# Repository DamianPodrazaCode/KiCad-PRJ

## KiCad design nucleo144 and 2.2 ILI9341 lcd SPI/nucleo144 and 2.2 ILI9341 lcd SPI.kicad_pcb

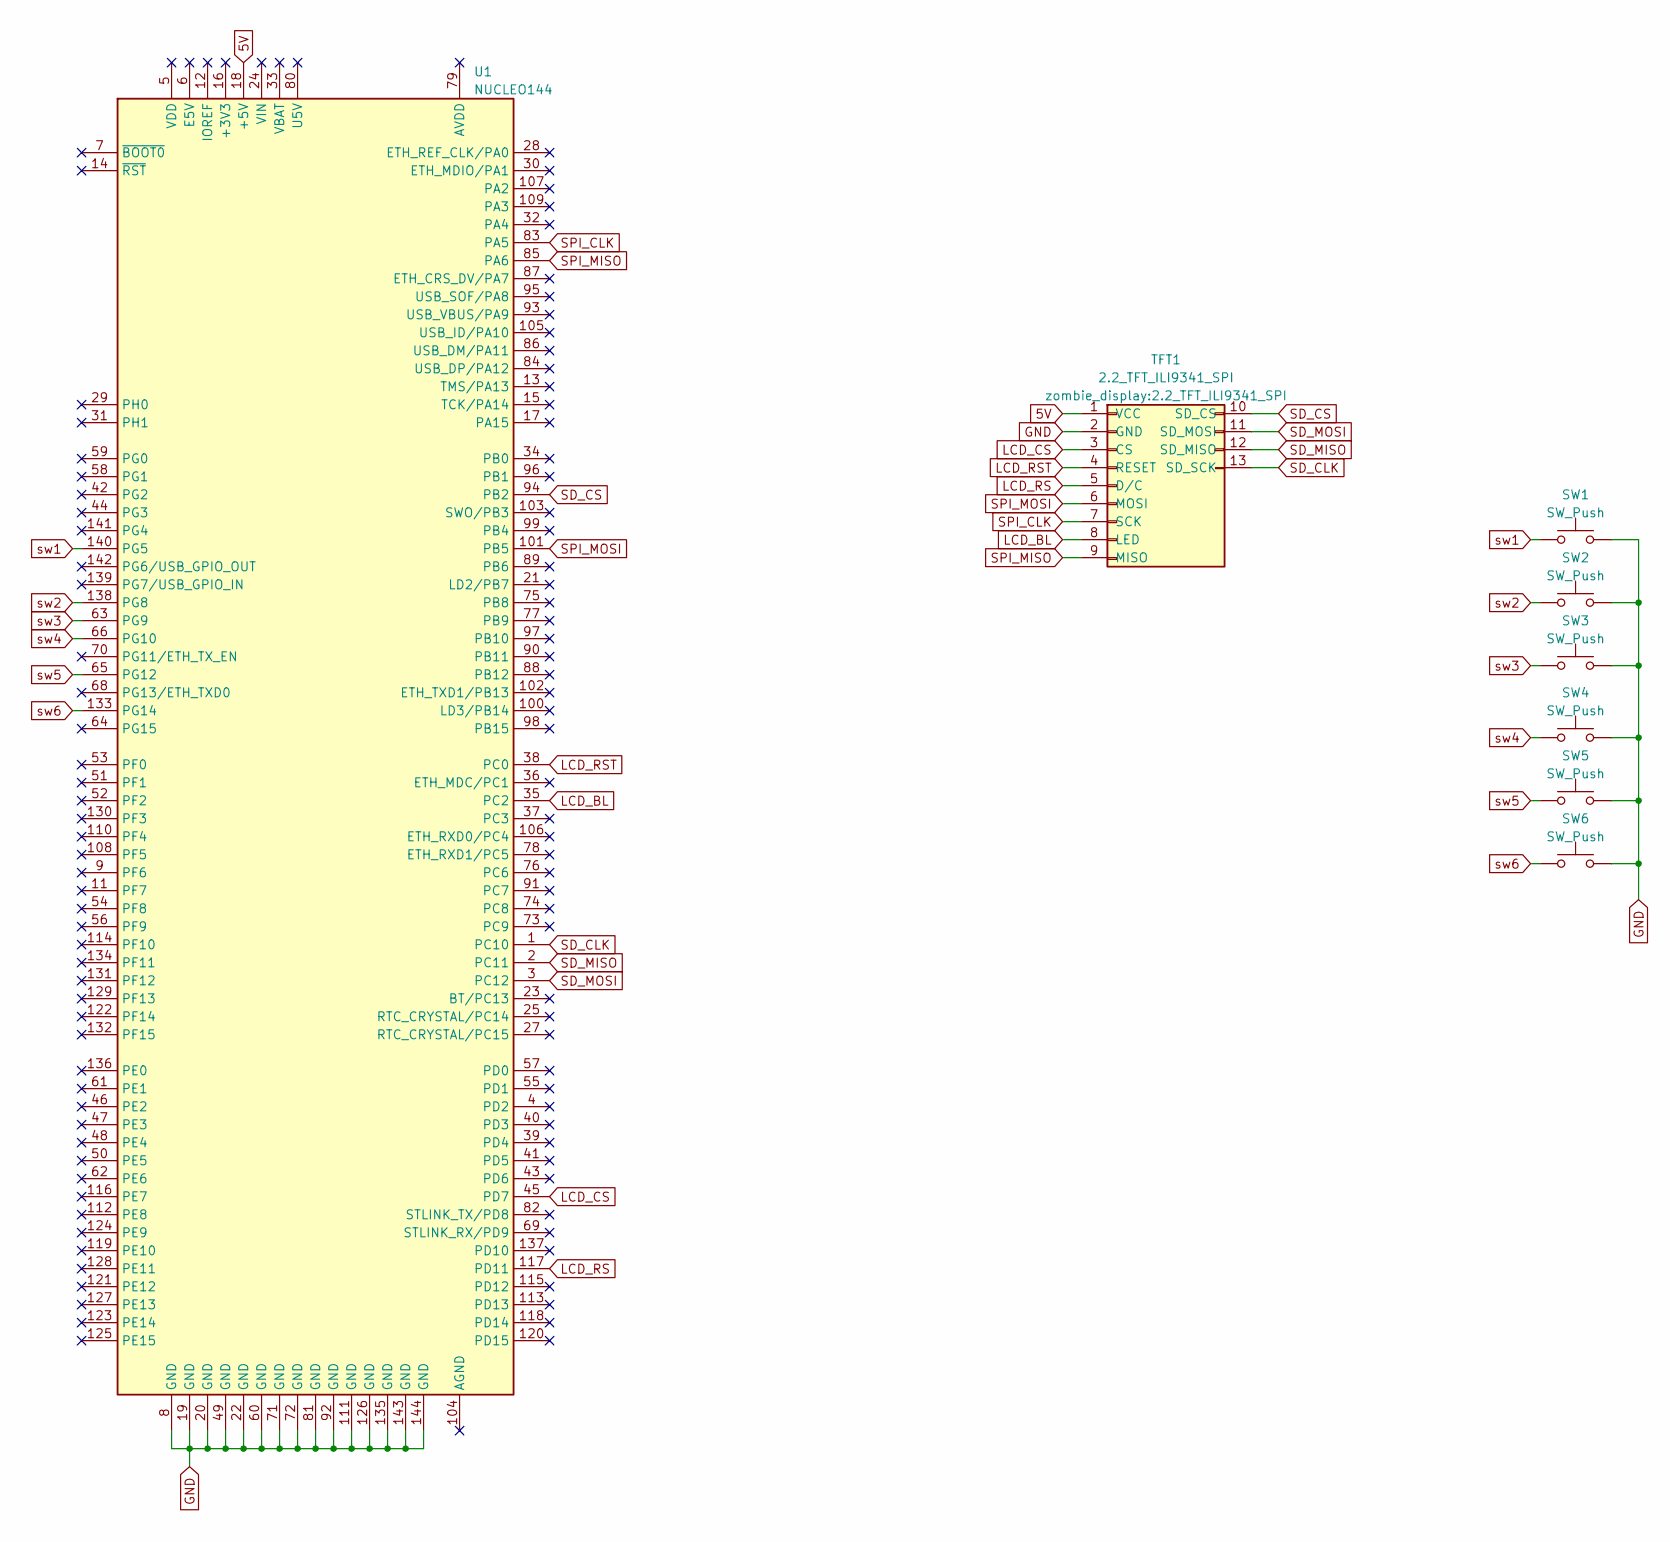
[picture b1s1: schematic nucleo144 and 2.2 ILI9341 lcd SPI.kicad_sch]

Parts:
SW1, SW2, SW3, SW4, SW5, SW6: SW_Push; SW_PUSH_6mm
TFT1: 2.2_TFT_ILI9341_SPI
U1: NUCLEO144; ST_Morpho_Connector_144_Short

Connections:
5V: TFT1.1 (VCC), U1.18 (+5V)
D0: U1.118 (PD14)
D1: U1.120 (PD15)
D2: U1.57 (PD0)
D3: U1.55 (PD1)
D4: U1.116 (PE7)
D5: U1.112 (PE8)
D6: U1.124 (PE9)
D7: U1.119 (PE10)
D8: U1.128 (PE11)
D9: U1.121 (PE12)
D10: U1.127 (PE13)
D11: U1.123 (PE14)
D12: U1.125 (PE15)
D13: U1.82 (STLINK_TX/PD8)
D14: U1.69 (STLINK_RX/PD9)
D15: U1.137 (PD10)
F_CS: U1.96 (PB1)
GND: SW1.2, SW2.2, SW3.2, SW4.2, SW5.2, SW6.2, TFT1.2 (GND), U1.8 (GND), U1.19 (GND), U1.20 (GND), U1.22 (GND), U1.49 (GND), U1.60 (GND), U1.71 (GND), U1.72 (GND), U1.81 (GND), U1.92 (GND), U1.111 (GND), U1.126 (GND), U1.135 (GND), U1.143 (GND), U1.144 (GND)
LCD_BL: TFT1.8 (LED), U1.35 (PC2)
LCD_CS: TFT1.3 (CS), U1.45 (PD7)
LCD_RD: U1.39 (PD4)
LCD_RS: TFT1.5 (D/C), U1.117 (PD11)
LCD_RST: TFT1.4 (RESET), U1.38 (PC0)
LCD_WR: U1.41 (PD5)
PEN: U1.37 (PC3)
SD_CLK: TFT1.13 (SD_SCK), U1.1 (PC10)
SD_CS: TFT1.10 (SD_CS), U1.94 (PB2)
SD_MISO: TFT1.12 (SD_MISO), U1.2 (PC11)
SD_MOSI: TFT1.11 (SD_MOSI), U1.3 (PC12)
SPI_CLK: TFT1.7 (SCK), U1.83 (PA5)
SPI_MISO: TFT1.9 (MISO), U1.85 (PA6)
SPI_MOSI: TFT1.6 (MOSI), U1.101 (PB5)
T_CS: U1.109 (PA3)
sw1: SW1.1, U1.140 (PG5)
sw2: SW2.1, U1.138 (PG8)
sw3: SW3.1, U1.63 (PG9)
sw4: SW4.1, U1.66 (PG10)
sw5: SW5.1, U1.65 (PG12)
sw6: SW6.1, U1.133 (PG14)

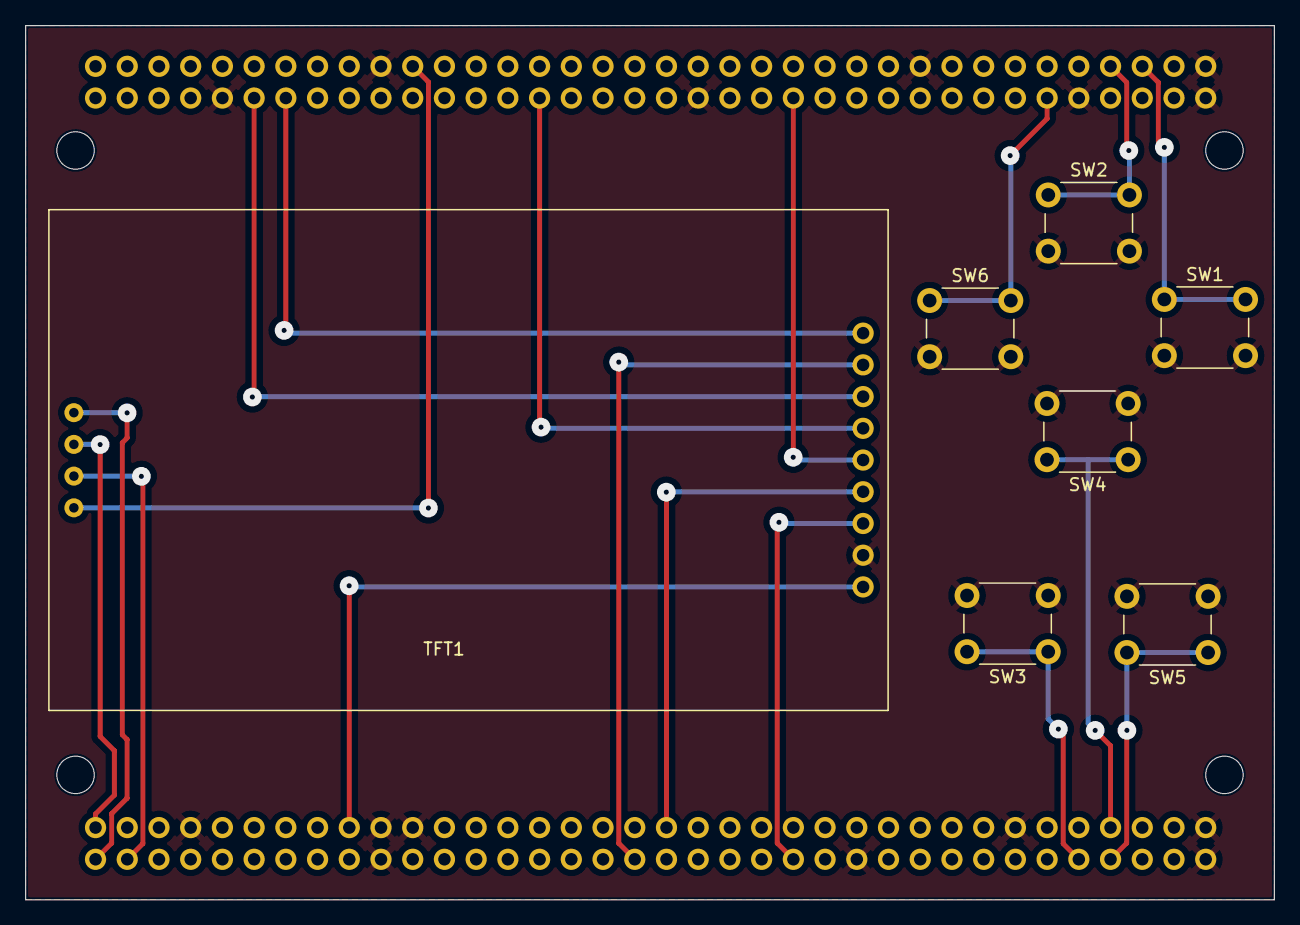
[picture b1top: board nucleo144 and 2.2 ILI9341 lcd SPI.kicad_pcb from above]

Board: 2 copper layers, 100.0 x 70.0 mm, 8 parts (0 on the bottom side), 19 nets.

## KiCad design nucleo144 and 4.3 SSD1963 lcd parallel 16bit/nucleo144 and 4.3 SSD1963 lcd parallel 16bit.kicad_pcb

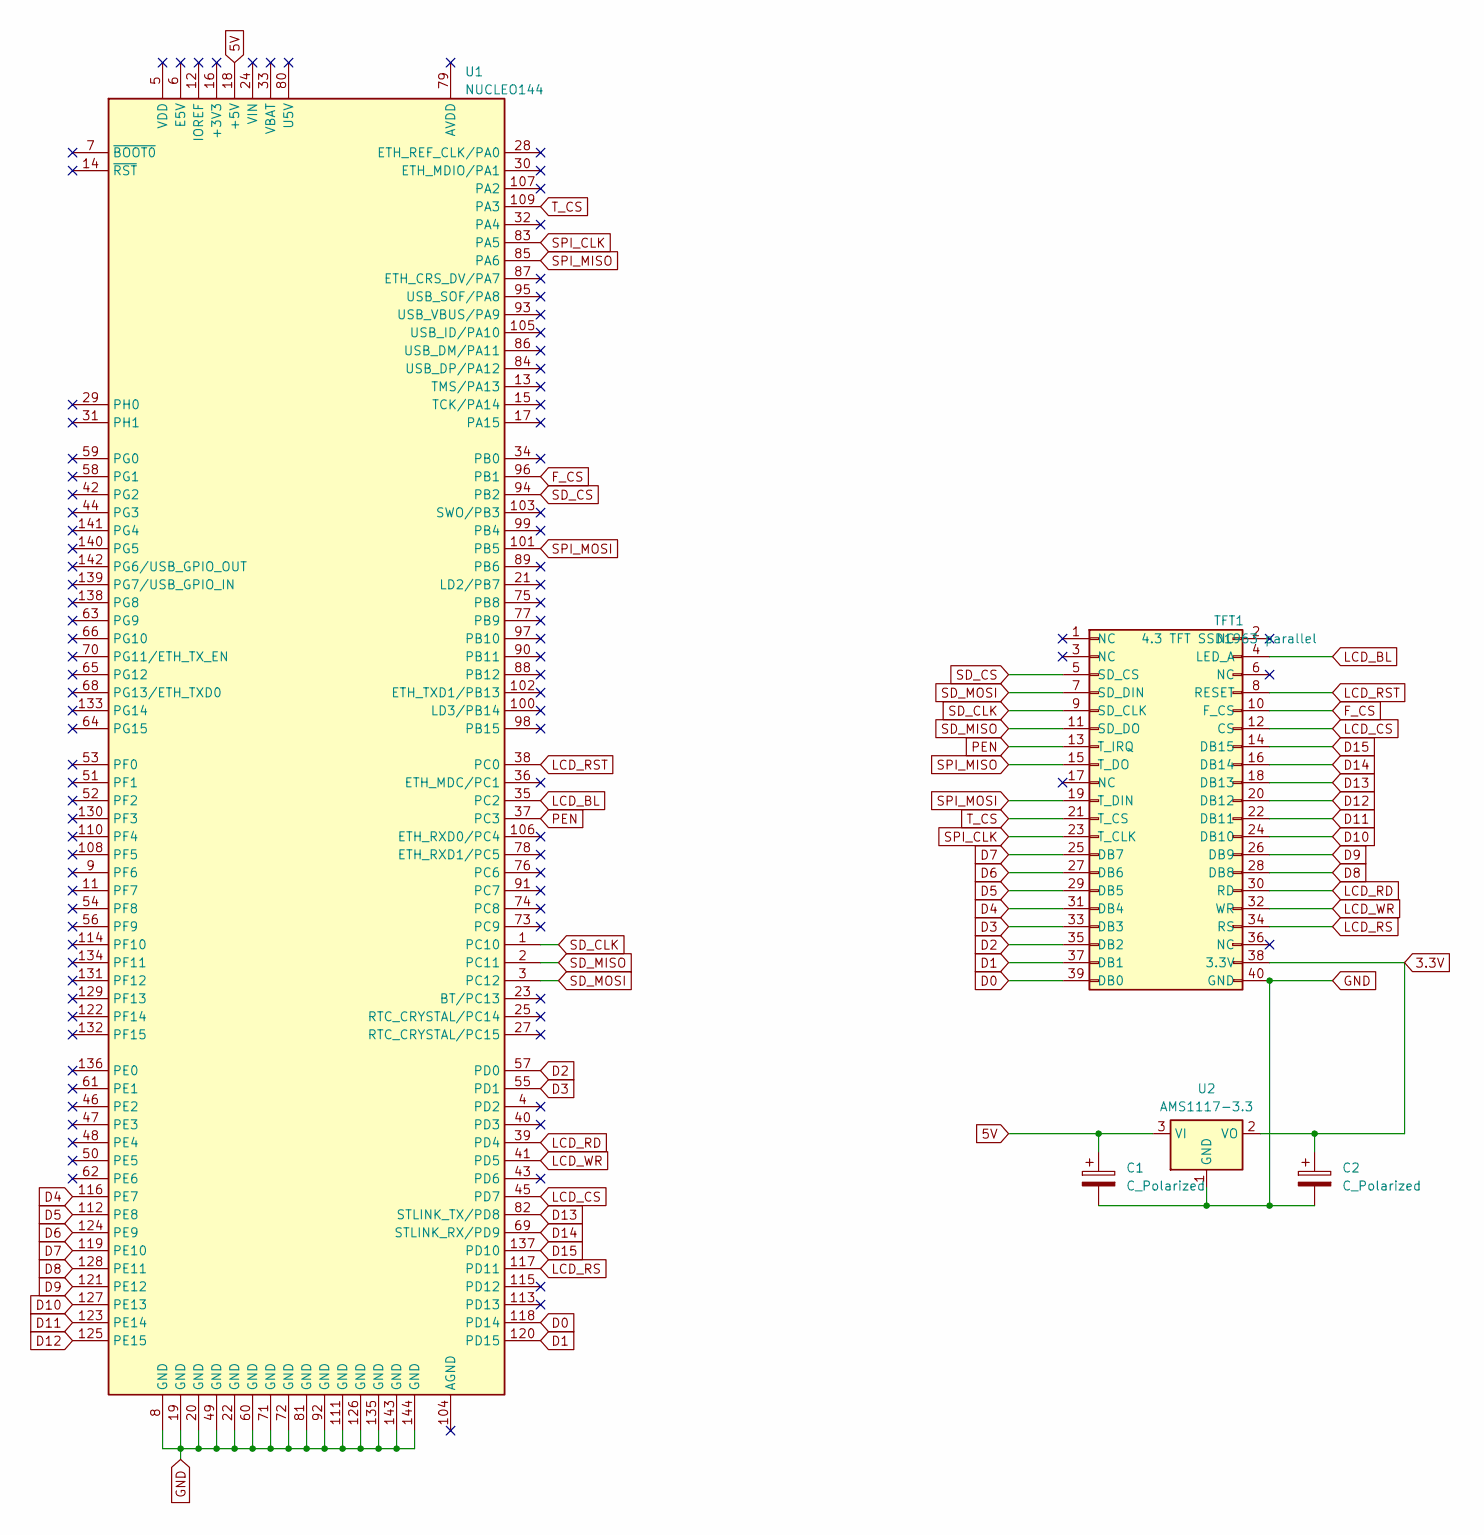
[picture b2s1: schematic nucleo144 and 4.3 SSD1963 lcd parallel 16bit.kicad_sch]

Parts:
C1, C2: C_Polarized; CP_EIA-3528-12_Kemet-T
TFT1: 4.3 TFT SSD1963 parallel; 4.3_TFT_SSD1963
U1: NUCLEO144; ST_Morpho_Connector_144_Short
U2: AMS1117-3.3; SOT-223-3_TabPin2

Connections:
3.3V: C2.1, TFT1.38 (3.3V), U2.2 (VO)
5V: C1.1, U1.18 (+5V), U2.3 (VI)
D0: TFT1.39 (DB0), U1.118 (PD14)
D1: TFT1.37 (DB1), U1.120 (PD15)
D2: TFT1.35 (DB2), U1.57 (PD0)
D3: TFT1.33 (DB3), U1.55 (PD1)
D4: TFT1.31 (DB4), U1.116 (PE7)
D5: TFT1.29 (DB5), U1.112 (PE8)
D6: TFT1.27 (DB6), U1.124 (PE9)
D7: TFT1.25 (DB7), U1.119 (PE10)
D8: TFT1.28 (DB8), U1.128 (PE11)
D9: TFT1.26 (DB9), U1.121 (PE12)
D10: TFT1.24 (DB10), U1.127 (PE13)
D11: TFT1.22 (DB11), U1.123 (PE14)
D12: TFT1.20 (DB12), U1.125 (PE15)
D13: TFT1.18 (DB13), U1.82 (STLINK_TX/PD8)
D14: TFT1.16 (DB14), U1.69 (STLINK_RX/PD9)
D15: TFT1.14 (DB15), U1.137 (PD10)
F_CS: TFT1.10 (F_CS), U1.96 (PB1)
GND: C1.2, C2.2, TFT1.40 (GND), U1.8 (GND), U1.19 (GND), U1.20 (GND), U1.22 (GND), U1.49 (GND), U1.60 (GND), U1.71 (GND), U1.72 (GND), U1.81 (GND), U1.92 (GND), U1.111 (GND), U1.126 (GND), U1.135 (GND), U1.143 (GND), U1.144 (GND), U2.1 (GND)
LCD_BL: TFT1.4 (LED_A), U1.35 (PC2)
LCD_CS: TFT1.12 (CS), U1.45 (PD7)
LCD_RD: TFT1.30 (RD), U1.39 (PD4)
LCD_RS: TFT1.34 (RS), U1.117 (PD11)
LCD_RST: TFT1.8 (RESET), U1.38 (PC0)
LCD_WR: TFT1.32 (WR), U1.41 (PD5)
PEN: TFT1.13 (T_IRQ), U1.37 (PC3)
SD_CLK: TFT1.9 (SD_CLK), U1.1 (PC10)
SD_CS: TFT1.5 (SD_CS), U1.94 (PB2)
SD_MISO: TFT1.11 (SD_DO), U1.2 (PC11)
SD_MOSI: TFT1.7 (SD_DIN), U1.3 (PC12)
SPI_CLK: TFT1.23 (T_CLK), U1.83 (PA5)
SPI_MISO: TFT1.15 (T_DO), U1.85 (PA6)
SPI_MOSI: TFT1.19 (T_DIN), U1.101 (PB5)
T_CS: TFT1.21 (T_CS), U1.109 (PA3)

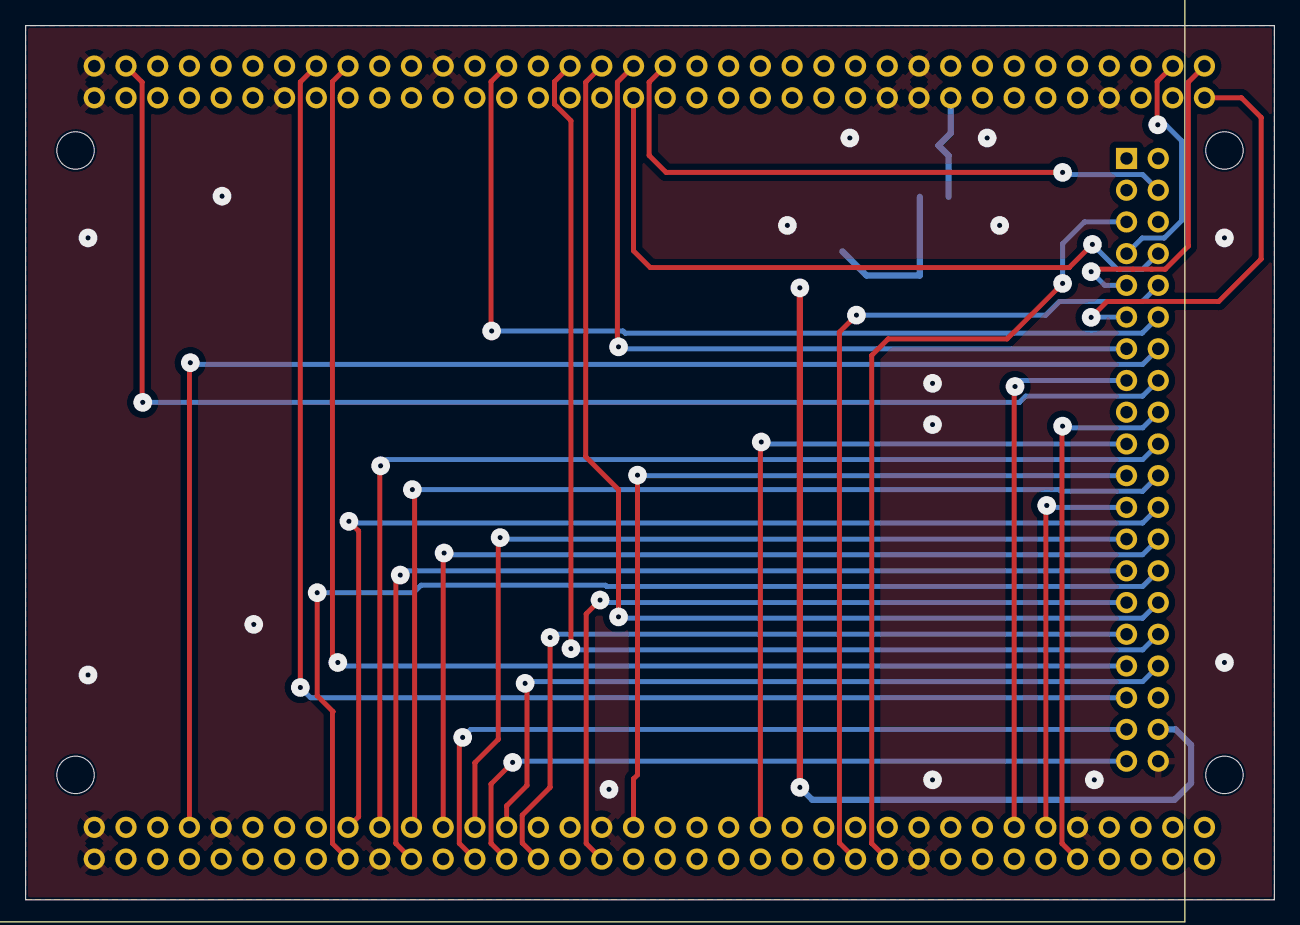
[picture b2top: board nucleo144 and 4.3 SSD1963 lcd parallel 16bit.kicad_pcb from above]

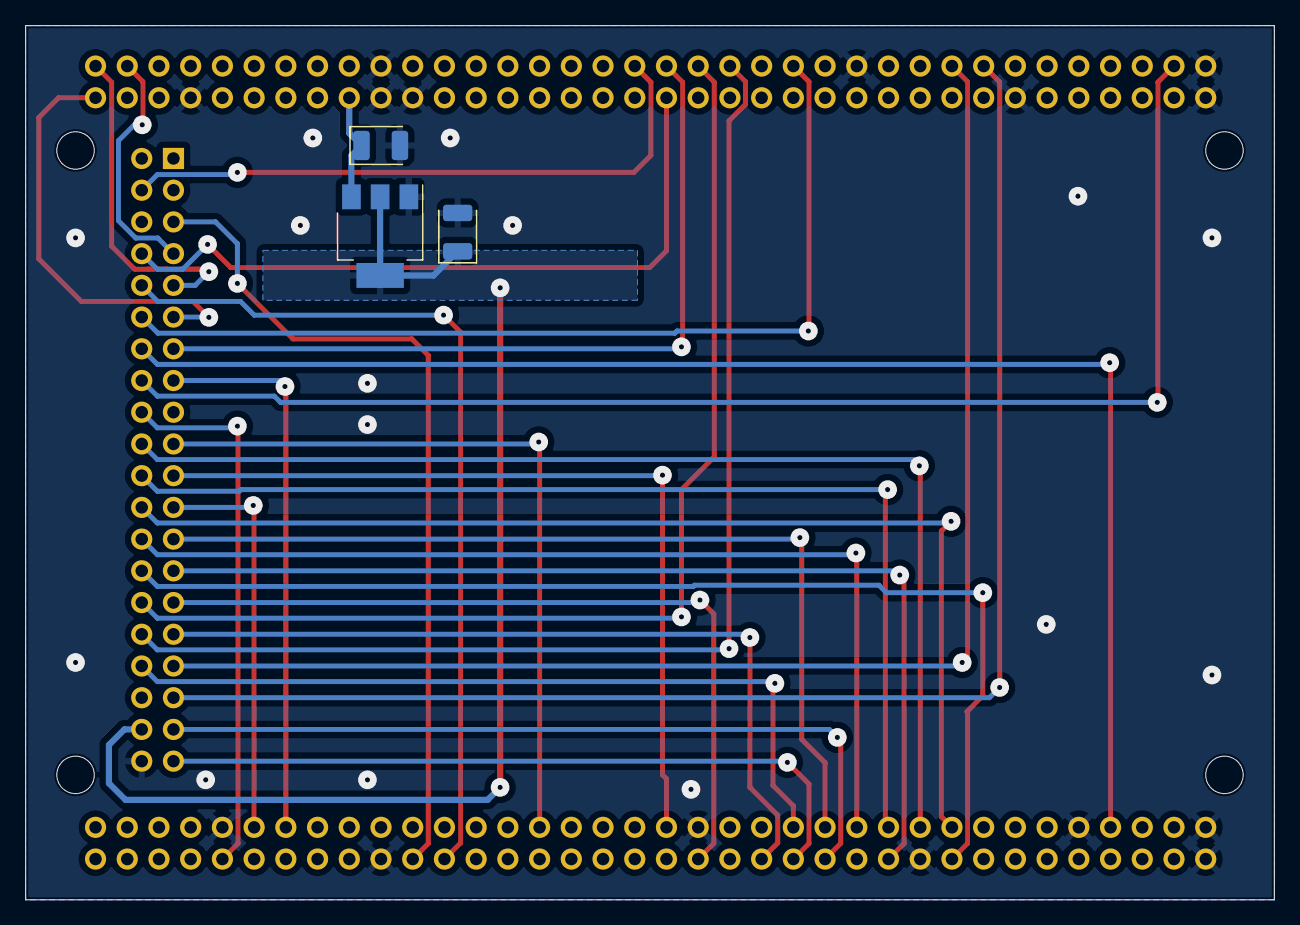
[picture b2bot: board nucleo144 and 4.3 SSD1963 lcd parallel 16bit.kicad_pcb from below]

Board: 2 copper layers, 100.0 x 70.0 mm, 5 parts (3 on the bottom side), 35 nets.

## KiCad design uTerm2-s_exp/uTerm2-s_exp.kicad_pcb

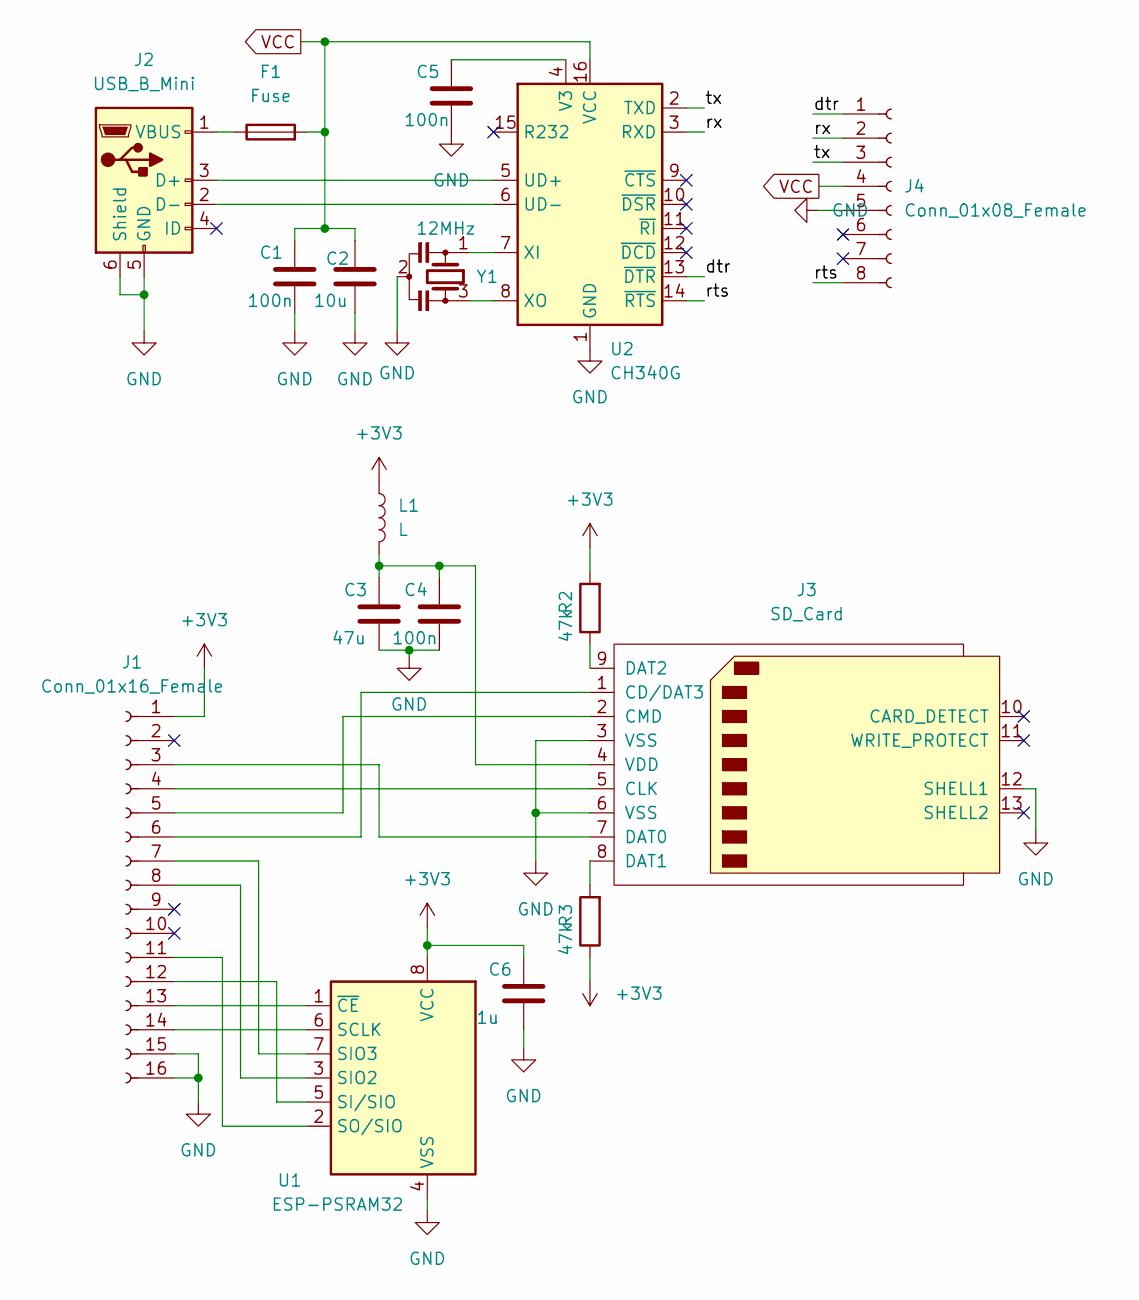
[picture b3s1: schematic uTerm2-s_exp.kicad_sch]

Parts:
C1, C4, C5: 100n; C_1206_3216Metric_Pad1.33x1.80mm_HandSolder
C2: 10u; C_1206_3216Metric_Pad1.33x1.80mm_HandSolder
C3: 47u; CP_EIA-3528-12_Kemet-T_Pad1.50x2.35mm_HandSolder
C6: 1u; C_1206_3216Metric_Pad1.33x1.80mm_HandSolder
F1: Fuse; Fuse_1812_4532Metric_Pad1.30x3.40mm_HandSolder
J1: Conn_01x16_Female; PinSocket_2x08_P2.54mm_Vertical
J2: USB_B_Mini; USB_Mini-B_Lumberg_2486_01_Horizontal
J3: SD_Card; SD_TE_2041021
J4: Conn_01x08_Female; PinSocket_1x08_P2.54mm_Vertical
L1: L; L_1806_4516Metric_Pad1.45x1.90mm_HandSolder
R2, R3: 47k; R_1206_3216Metric_Pad1.30x1.75mm_HandSolder
U1: ESP-PSRAM32; SOIC-8_3.9x4.9mm_P1.27mm
U2: CH340G; SOP-16_3.9x9.9mm_P1.27mm
Y1: 12MHz; Resonator_SMD_Murata_CSTxExxV-3Pin_3.0x1.1mm_HandSoldering

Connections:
+3V3: C6.1, J1.1, L1.1, R2.2, R3.1, U1.8 (VCC)
/dtr: J4.1, U2.13 (~DTR)
/rts: J4.8, U2.14 (~RTS)
/rx: J4.2, U2.3 (RXD)
/tx: J4.3, U2.2 (TXD)
GND: C1.2, C2.2, C3.2, C4.2, C5.2, C6.2, J1.15, J1.16, J2.5 (GND), J2.6 (Shield), J3.3 (VSS), J3.6 (VSS), J3.12 (SHELL1), J4.5, U1.4 (VSS), U2.1 (GND), Y1.2
unnamed: C3.1, C4.1, J3.4 (VDD), L1.2
unnamed: C5.1, U2.4 (V3)
unnamed: F1.1, J2.1 (VBUS)
unnamed: J1.3, J3.7 (DAT0)
unnamed: J1.4, J3.5 (CLK)
unnamed: J1.5, J3.2 (CMD)
unnamed: J1.6, J3.1 (CD/DAT3)
unnamed: J1.7, U1.7 (SIO3)
unnamed: J1.8, U1.3 (SIO2)
unnamed: J1.11, U1.2 (SO/SIO)
unnamed: J1.12, U1.5 (SI/SIO)
unnamed: J1.13, U1.1 (~CE)
unnamed: J1.14, U1.6 (SCLK)
unnamed: J2.2 (D-), U2.6 (UD-)
unnamed: J2.3 (D+), U2.5 (UD+)
unnamed: J3.8 (DAT1), R3.2
unnamed: J3.9 (DAT2), R2.1
unnamed: U2.7 (XI), Y1.1
unnamed: U2.8 (XO), Y1.3
VCC: C1.1, C2.1, F1.2, J4.4, U2.16 (VCC)

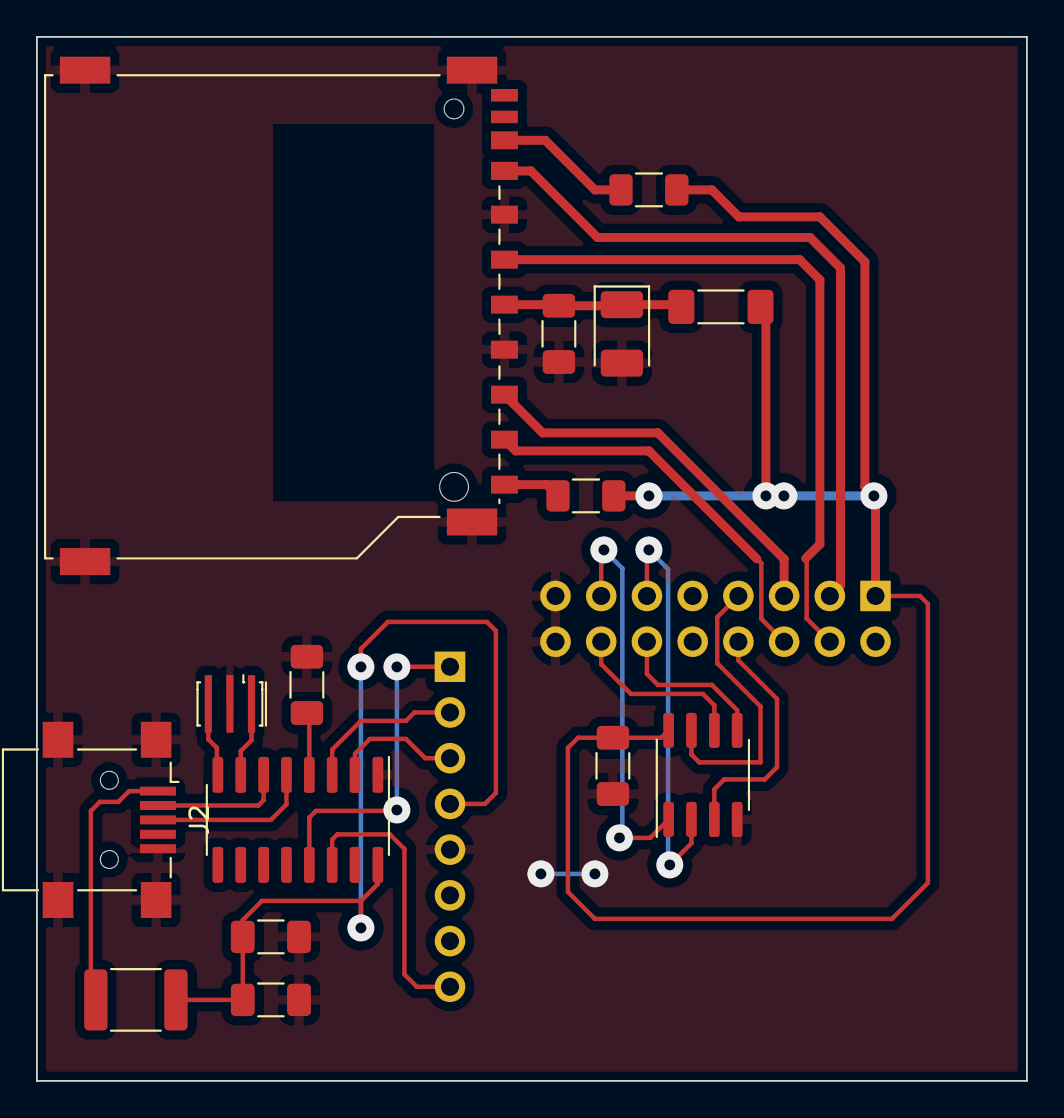
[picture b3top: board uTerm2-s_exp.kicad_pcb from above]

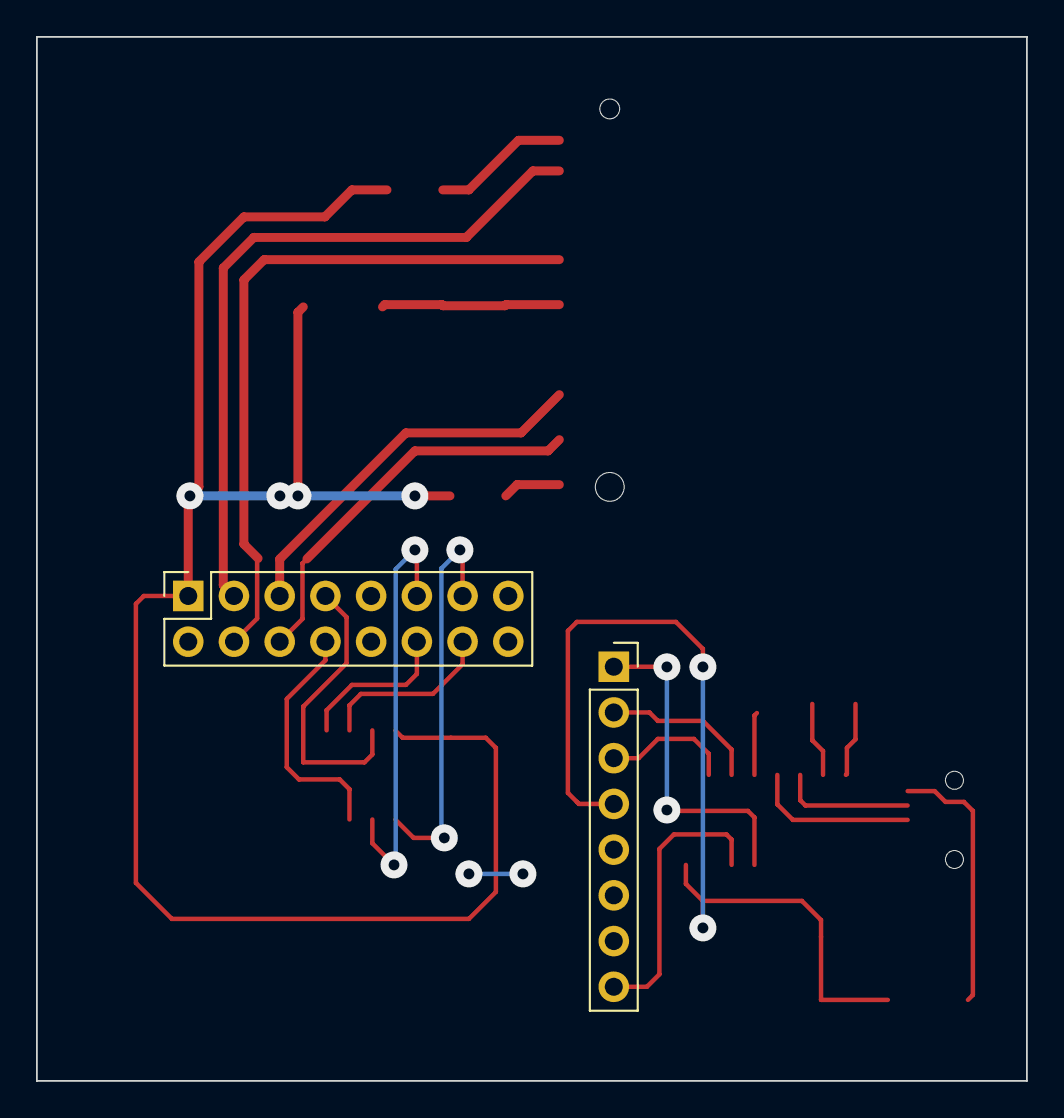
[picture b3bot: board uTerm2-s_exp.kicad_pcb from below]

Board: 2 copper layers, 55.0 x 58.0 mm, 17 parts (2 on the bottom side), 26 nets.

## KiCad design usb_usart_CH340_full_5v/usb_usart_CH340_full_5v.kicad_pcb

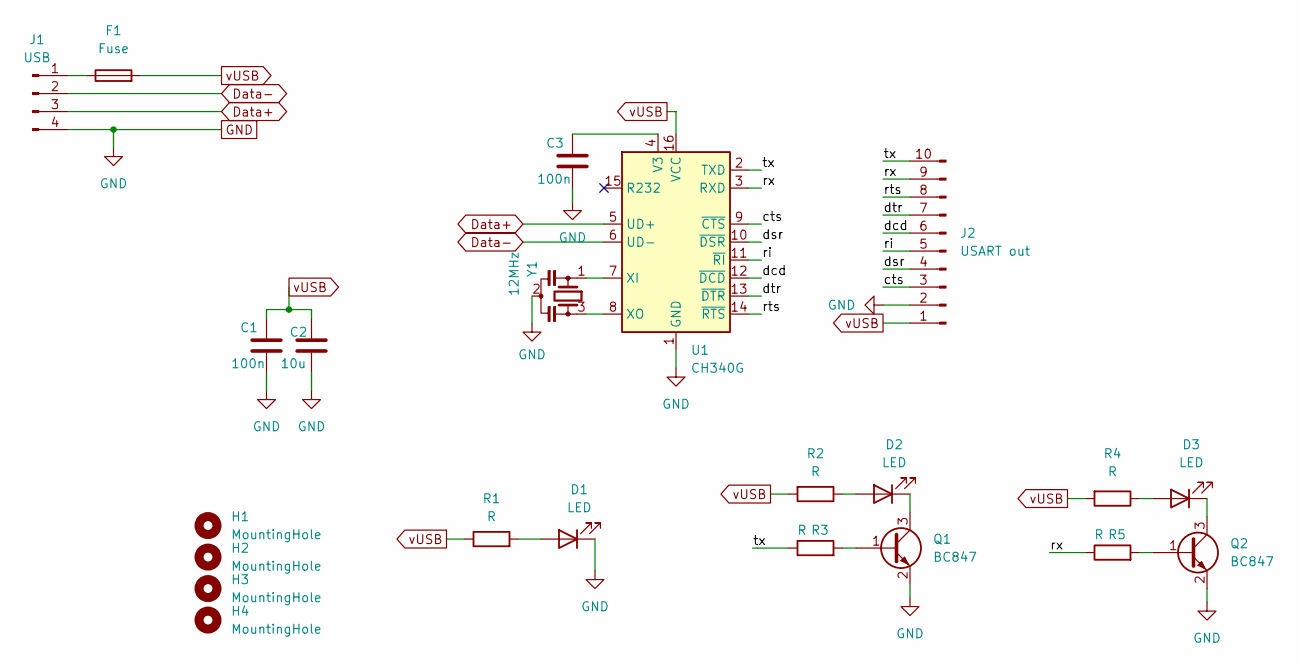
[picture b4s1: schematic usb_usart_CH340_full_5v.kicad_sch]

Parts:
C1, C3: 100n; C_1206_3216Metric_Pad1.33x1.80mm_HandSolder
C2: 10u; C_1206_3216Metric_Pad1.33x1.80mm_HandSolder
D1, D2, D3: LED; LED_0805_2012Metric_Pad1.15x1.40mm_HandSolder
F1: Fuse; Fuse_1812_4532Metric_Pad1.30x3.40mm_HandSolder
H1, H2, H3, H4: MountingHole; MountingHole_3mm_Pad_TopOnly
J1: USB; PinHeader_1x04_P2.54mm_Horizontal
J2: USART out; PinSocket_1x10_P2.54mm_Horizontal
Q1, Q2: BC847; SOT-23
R1, R2, R3, R4, R5: R; R_1206_3216Metric_Pad1.30x1.75mm_HandSolder
U1: CH340G; SOP-16_3.9x9.9mm_P1.27mm
Y1: 12MHz; Resonator_SMD_Murata_CSTxExxV-3Pin_3.0x1.1mm_HandSoldering

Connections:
/cts: J2.3, U1.9 (~CTS)
/dcd: J2.6, U1.12 (~DCD)
/dsr: J2.4, U1.10 (~DSR)
/dtr: J2.7, U1.13 (~DTR)
/ri: J2.5, U1.11 (~RI)
/rts: J2.8, U1.14 (~RTS)
/rx: J2.9, R5.1, U1.3 (RXD)
/tx: J2.10, R3.1, U1.2 (TXD)
Data+: J1.3, U1.5 (UD+)
Data-: J1.2, U1.6 (UD-)
GND: C1.2, C2.2, C3.2, D1.1 (K), J1.4, J2.2, Q1.2 (E), Q2.2 (E), U1.1 (GND), Y1.2
unnamed: C3.1, U1.4 (V3)
unnamed: D1.2 (A), R1.2
unnamed: D2.1 (K), Q1.3 (C)
unnamed: D2.2 (A), R2.1
unnamed: D3.1 (K), Q2.3 (C)
unnamed: D3.2 (A), R4.1
unnamed: F1.1, J1.1
unnamed: Q1.1 (B), R3.2
unnamed: Q2.1 (B), R5.2
unnamed: U1.7 (XI), Y1.1
unnamed: U1.8 (XO), Y1.3
vUSB: C1.1, C2.1, F1.2, J2.1, R1.1, R2.2, R4.2, U1.16 (VCC)

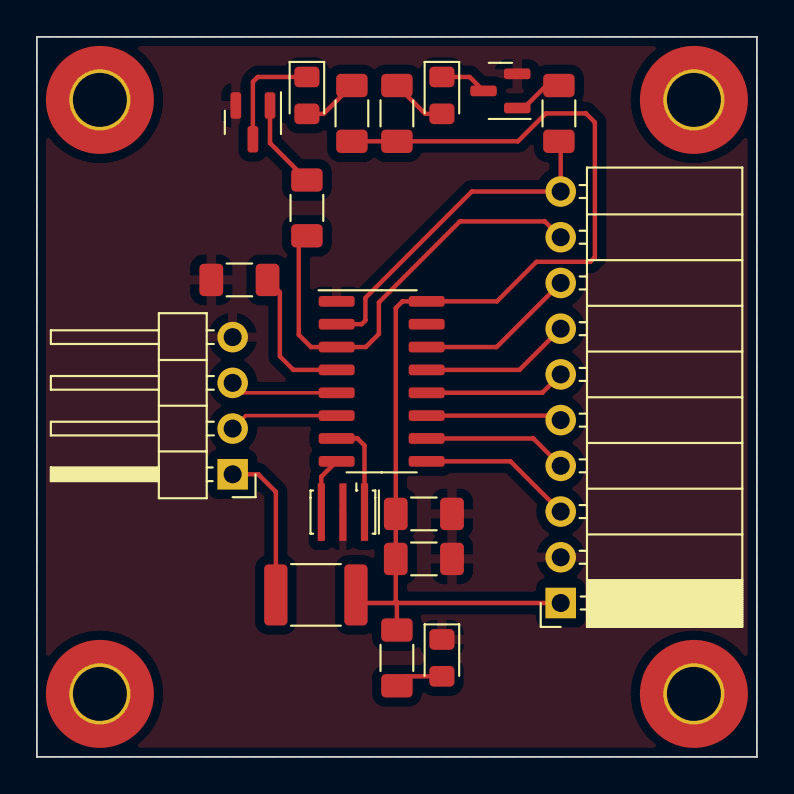
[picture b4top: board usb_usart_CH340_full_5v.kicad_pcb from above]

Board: 2 copper layers, 40.0 x 40.0 mm, 22 parts (0 on the bottom side), 23 nets.
